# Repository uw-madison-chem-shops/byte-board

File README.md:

# Byte Board

Small circuit board project designed to practice soldering in UW-Madison Chemistry Shops.

## PCB

This PCB was designed using KiCad 7.

See `byte.pdf` for schematic.

Printed circuit board fabrication files can be found in the gerber directory.
PCB images generated with [tracespace](https://github.com/tracespace/tracespace) follow.

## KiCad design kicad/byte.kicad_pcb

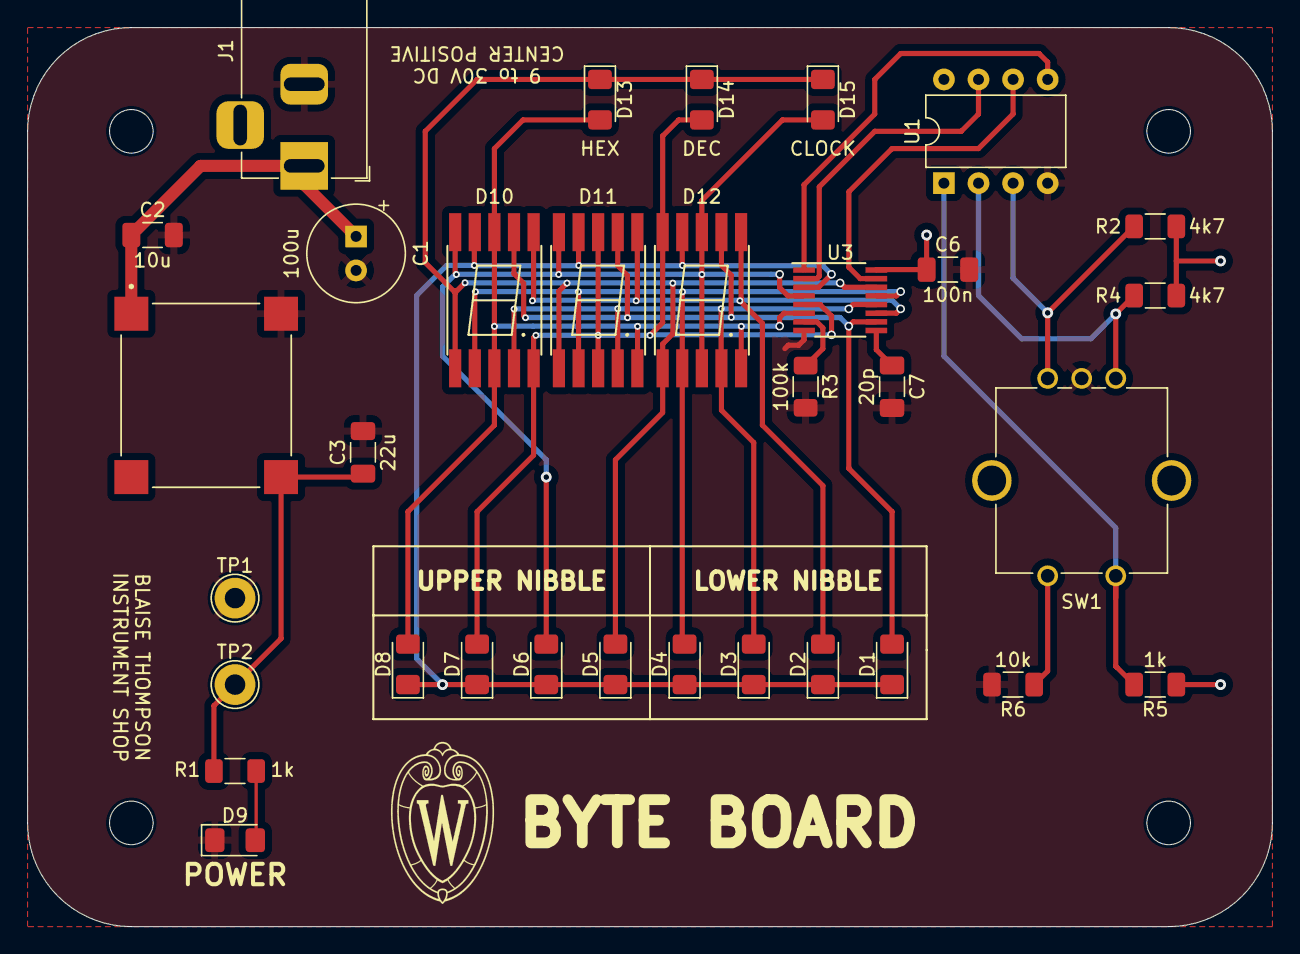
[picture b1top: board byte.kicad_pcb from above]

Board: 2 copper layers, 91.4 x 66.0 mm, 33 parts (0 on the bottom side), 22 nets.

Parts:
C1: 100u; CP_Radial_Tantal_D7.0mm_P2.50mm
C2: 10u; C_1206_3216Metric_Pad1.33x1.80mm_HandSolder
C3: 22u; C_1206_3216Metric_Pad1.33x1.80mm_HandSolder
C6: 100n; C_1206_3216Metric_Pad1.33x1.80mm_HandSolder
C7: 20p; C_1206_3216Metric_Pad1.33x1.80mm_HandSolder
D1, D2, D3, D4, D5, D6, D7, D8, D9: LED; LED_1206_3216Metric_Pad1.42x1.75mm_HandSolder
D10, D11, D12: ACSC02-41SURKWA-F01
D13: HEX; LED_1206_3216Metric_Pad1.42x1.75mm_HandSolder
D14: DEC; LED_1206_3216Metric_Pad1.42x1.75mm_HandSolder
D15: CLOCK; LED_1206_3216Metric_Pad1.42x1.75mm_HandSolder
J1: Barrel_Jack; BarrelJack_Horizontal
PS1: VXO7803-500-M; CONV_VXO7805-500-M
R1, R5: 1k; R_1206_3216Metric_Pad1.30x1.75mm_HandSolder
R2, R4: 4k7; R_1206_3216Metric_Pad1.30x1.75mm_HandSolder
R3: 100k; R_1206_3216Metric_Pad1.30x1.75mm_HandSolder
R6: 10k; R_1206_3216Metric_Pad1.30x1.75mm_HandSolder
SW1: RotaryEncoder_Switch; RotaryEncoder_Bourns_Vertical_PEC12R-3xxxF-Sxxxx
TP1, TP2: TestPoint; TestPoint_THTPad_D3.0mm_Drill1.5mm
U1: ATtiny85-20P; DIP-8_W7.62mm
U3: MAX6951; QSOP-16_3.9x4.9mm_P0.635mm

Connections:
+3V3: C3.1, C6.1, PS1.3 (+VO), R1.1, R2.1, R4.1, R5.1, TP2.1, U1.8 (VCC), U3.16 (V+)
/LED_driver/SEG0: D8.2 (A), D10.3 (C.K.), D10.8 (C.K.), D11.5 (DP), D12.5 (DP), D13.2 (A), U3.6 (DIG0/SEG0)
/LED_driver/SEG1: D7.2 (A), D10.5 (DP), D11.3 (C.K.), D11.8 (C.K.), D12.10 (g), D14.2 (A), U3.5 (DIG1/SEG1)
/LED_driver/SEG2: D6.2 (A), D10.10 (g), D11.10 (g), D12.3 (C.K.), D12.8 (C.K.), D15.2 (A), U3.4 (DIG2/SEG2)
/LED_driver/SEG3: D1.1 (K), D2.1 (K), D3.1 (K), D4.1 (K), D5.1 (K), D6.1 (K), D7.1 (K), D8.1 (K), D10.9 (f), D11.9 (f), D12.9 (f), U3.3 (DIG3/SEG3)
/LED_driver/SEG4: D5.2 (A), D10.1 (e), D11.1 (e), D12.1 (e), D13.1 (K), D14.1 (K), D15.1 (K), U3.14 (DIG4/SEG4)
/LED_driver/SEG5: D4.2 (A), D10.2 (d), D11.2 (d), D12.2 (d), U3.13 (DIG5/SEG5)
/LED_driver/SEG6: D3.2 (A), D10.4 (c), D11.4 (c), D12.4 (c), U3.12 (DIG6/SEG6)
/LED_driver/SEG7: D2.2 (A), D10.6 (b), D11.6 (b), D12.6 (b), U3.11 (DIG7/SEG7)
/LED_driver/SEG8: D1.2 (A), D10.7 (a), D11.7 (a), D12.7 (a), U3.10 (SEG8)
A: R4.2, SW1.A, U1.2 (XTAL1/PB3)
B: R2.2, SW1.B, U1.3 (XTAL2/PB4)
CLK: U1.7 (PB2), U3.2 (CLK)
CS: U1.6 (PB1), U3.15 (~CS)
GND: C1.2, C2.2, C3.2, C6.2, C7.2, D9.1 (K), J1.2, PS1.2 (GND), R3.2, R6.2, SW1.C, TP1.1, U1.4 (GND), U3.8 (GND)
MOSI: U1.5 (AREF/PB0), U3.1 (DIN)
unnamed: D9.2 (A), R1.2
unnamed: C1.1, C2.1, J1.1, PS1.1 (+VIN)
unnamed: R6.1, SW1.S2
unnamed: R3.1, U3.7 (ISET)
unnamed: C7.1, U3.9 (OSC)
SWITCH: R5.2, SW1.S1, U1.1 (~RESET/PB5)

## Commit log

2023-03-22 revA
2023-06-06 revB
2023-06-16 schematic
2023-07-18 firmware
2023-07-20 Overflows to 0
2023-07-20 Overflow
2023-07-20 Overflow (#3)
    * Add files via upload
    * Overflows to 0
    * Overflow
2024-01-16 revC
